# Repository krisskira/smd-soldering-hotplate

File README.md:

# HotPlate

An open SMD reflow station. Instead of heating by eye, it runs a **Soldering Profile**: a precise temperature curve, step by step. It ramps under control, holds each plateau for the right time, signals when it is done and cools down on its own.

[Site](https://krisskira.github.io/smd-soldering-hotplate/) · [HotPanel and Studio](#two-ways-to-run-it) · [Docs](docs/README.md) · [Email](mailto:krisskira@gmail.com) · [Leer en español](README.es.md)

## What it does

- **HEAT** runs the whole profile from one gesture: optional wait, preheat, up to four rising or flat steps, then cooldown.
- **Scheduled start** waits from 00:00 (immediate) up to 12:00 before the cycle begins.
- **Predictive PI** cuts power before the target, so the plate's own inertia does not overshoot.
- **Autotune**, launched from HotPlate Studio, learns how the plate responds and stores the gains.
- **Safety** keeps the heater off at boot. A sensor fault or a reading above `temp_max_c` cuts the output at once.

## Two ways to run it

- **HotPanel**, the onboard interface: a large temperature, two tiles and a knob. Turn to choose, press to confirm. Heat starts or stops the cycle. Settings edits the four steps and the wait clock.
- **HotPlate Studio**, the desktop app over USB: live temperature chart, profile editing, CSV export, autotune and the limits the panel does not expose. When Studio takes control, HotPanel shows **USB** and local input locks. The two modes never run together.

## What's in the repo

- [`firmware/avr/`](firmware/avr/) — ATmega16 firmware at 8 MHz. The map of docs and code starts at [product features](firmware/avr/doc/product_features.md), [program flows](firmware/avr/doc/program_flows.md) and [architecture](firmware/avr/doc/architecture.md).
- [`hotplate-studio/`](hotplate-studio/) — HotPlate Studio (Python). The screens it follows are in [`hotplate-studio/design/`](hotplate-studio/design/).
- [`hardware/`](hardware/) — KiCad board and datasheets.
- [`mechanical/`](mechanical/) — 3D enclosure, covers and knob.
- [`landing-page/`](landing-page/) — the public site, React and TypeScript on Vite.

Flash is 16 KB. Thermal control, safety and the approved UI come first. See the [feature budget](firmware/avr/doc/feature_budget.md).

## Build

```bash
cd firmware/avr && make clean && make && make size && make usb-host-test

cd hotplate-studio && pip install -r requirements.txt && python app.py

cd landing-page && npm install && npm run dev
```

The site publishes to GitHub Pages from `.github/workflows/pages.yml` on every push to `main` that touches `landing-page/`. In the repository: **Settings → Pages → Source: GitHub Actions**.

## License

Open hardware and software. Use, study, modify and share it at your own risk. It works with mains power and high temperatures.

| What | License |
|------|---------|
| Firmware and HotPlate Studio | [MIT](LICENSE) |
| Board and 3D models | [CERN-OHL-P-2.0](LICENSE) |
| Docs and icons | [CC BY 4.0](LICENSE) |

The full text is in [LICENSE](LICENSE).

Author: **Crhistian David Vergara Gómez** · **krisskira@gmail.com**

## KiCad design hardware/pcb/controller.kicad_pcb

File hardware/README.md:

# Hardware

## PCB (`pcb/`)

Proyecto KiCad de **HotPlate**:

- `controller.*` — placa de control (ATmega16, LCD, encoder, MAX31865, …)
- `power-stage.*` — etapa de potencia / SSR
- `smd-soldering-hotplate-pcb.csv` — BOM
- `pcb-cnc/` — exports CNC si aplica

Abrir los `.kicad_pro` con KiCad 8+.

## Datasheets (`datasheets/`)

PDFs de referencia: ATmega16, MAX31865, MOC3021, BT136, ST7920, CH340, HLK-PM01, etc.

Pines de firmware: `firmware/avr/doc/atmega16_pin_definition_hotplate.md` ↔ `firmware/avr/config/board_pins.h`.

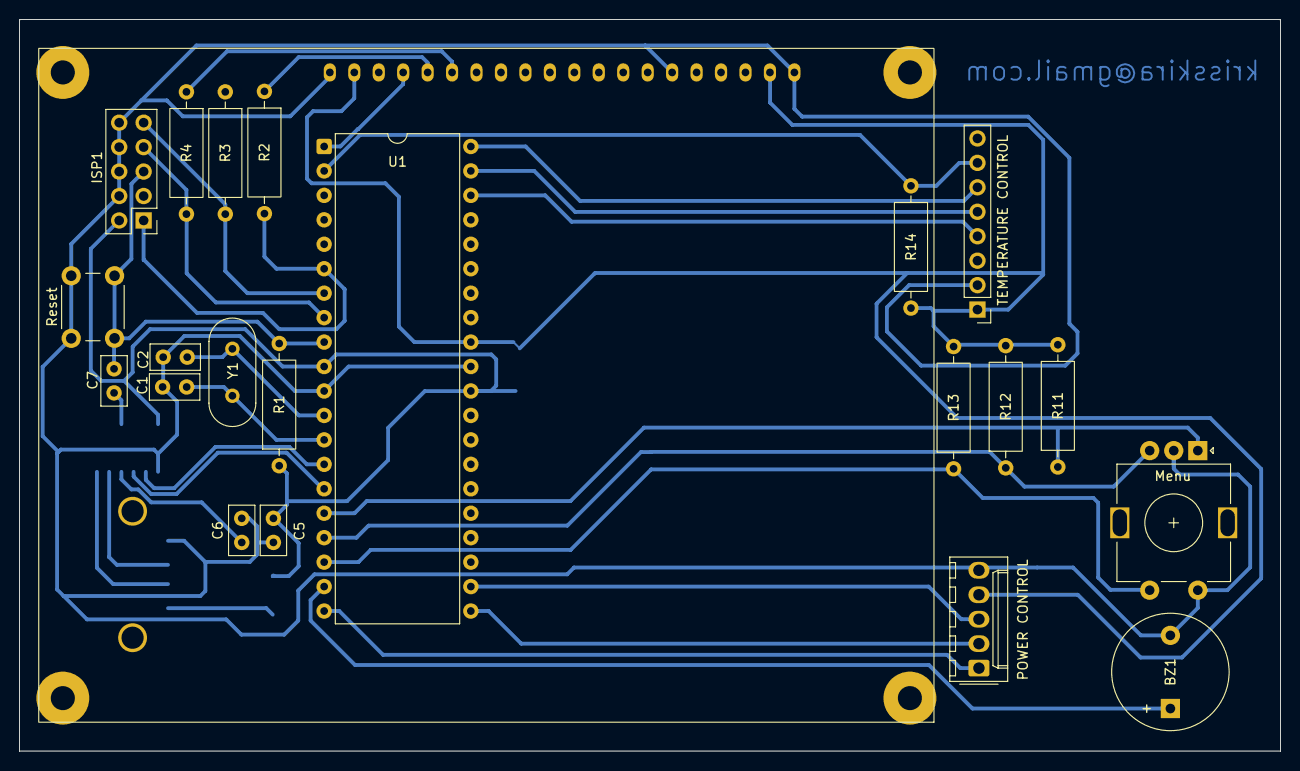
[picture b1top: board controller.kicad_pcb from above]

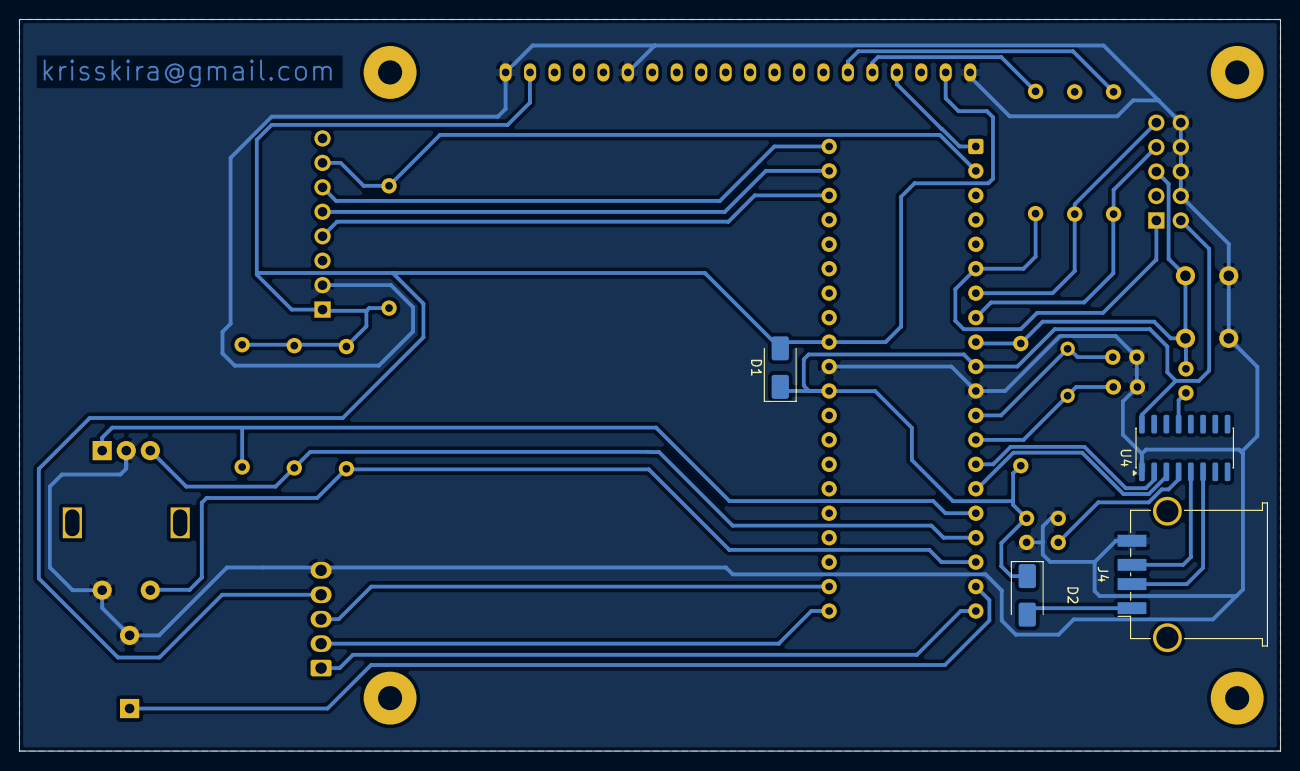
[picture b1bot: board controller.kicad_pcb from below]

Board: 2 copper layers, 131.0 x 76.0 mm, 26 parts (4 on the bottom side), 30 nets.

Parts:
BZ1: Buzzer; Buzzer_12x9.5RM7.6
C1, C2: 27pf; C_Disc_D5.0mm_W2.5mm_P2.50mm
C5, C6: 0.1uF; C_Disc_D5.0mm_W2.5mm_P2.50mm
C7: 100nF; C_Disc_D5.0mm_W2.5mm_P2.50mm
D1, D2: SS14; D_SMA
ISP1: Conn_02x05_Odd_Even; PinHeader_2x05_P2.54mm_Vertical
J4: USB_A; USB_A_TE_292303-7_Horizontal
LCD1: ST7920-12864B; st7920-12864b-v2
Menu: RotaryEncoder_Switch; RotaryEncoder_Alps_EC11E-Switch_Vertical_H20mm
POWER CONTROL: Conn_01x05_Pin; Molex_KK-254_AE-6410-05A_1x05_P2.54mm_Vertical
R1, R3, R4, R11, R12, R13, R14: 10K; R_Axial_DIN0309_L9.0mm_D3.2mm_P12.70mm_Horizontal
R2: 330; R_Axial_DIN0309_L9.0mm_D3.2mm_P12.70mm_Horizontal
Reset: SW_Push_Dual_x2; SW_PUSH_6mm_H5mm
TEMPERATURE CONTROL: Max31865; PinHeader_1x08_P2.54mm_Vertical
U1: ATmega16L-8P; DIP-40_W15.24mm
U4: CH340C; SOIC-16_3.9x9.9mm_P1.27mm
Y1: 16Mhz; Crystal_HC49-4H_Vertical

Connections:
+5V: D1.2 (A), LCD1.2 (VCC), LCD1.19 (BLA), POWER CONTROL.4, R11.2, R12.2, R13.2, R14.2, TEMPERATURE CONTROL.1, U1.32 (AREF)
BUZZER: BZ1.1 (+), U1.19 (PD5)
CS_MAX31865: R14.1, TEMPERATURE CONTROL.7, U1.2 (PB1)
FAN: POWER CONTROL.3, U1.22 (PC0)
GNDREF: BZ1.2 (-), C1.2, C2.2, C5.1, C6.2, ISP1.4, ISP1.6, ISP1.8, ISP1.10, J4.4 (GND), LCD1.1 (GND), LCD1.15 (PSB), LCD1.20 (BLK), Menu.C, Menu.S2, POWER CONTROL.5, Reset.1 (C), TEMPERATURE CONTROL.2, U1.11 (GND), U1.31 (GND), U4.1 (GND)
ICSP_CLK: ISP1.7, R4.2, U1.8 (PB7)
ICSP_MISO: ISP1.9, R3.2, U1.7 (PB6)
ICSP_MOSI: ISP1.1, R2.2, U1.6 (PB5)
ICSP_RST: C7.1, ISP1.5, R1.2, Reset.2 (D), U1.9 (~RESET)
LCD_RS: LCD1.4 (RS(CS*)), U1.1 (PB0)
MENU_CLK: Menu.A, R11.1, U1.16 (PD2)
MENU_DT: Menu.B, R12.1, U1.17 (PD3)
MENU_SW: Menu.S1, R13.1, U1.18 (PD4)
MOSI: LCD1.5 (R/W(SID*)), R2.1
unnamed: D2.2 (A), J4.1 (VBUS)
unnamed: J4.3 (D+), U4.5 (UD+)
unnamed: J4.2 (D-), U4.6 (UD-)
unnamed: C6.1, U4.4 (V3)
unnamed: C7.2, U4.13 (~DTR)
PTC1: POWER CONTROL.2, U1.21 (PD7)
PTC2: POWER CONTROL.1, U1.20 (PD6)
RX: U1.14 (PD0), U4.2 (TXD)
SCK: LCD1.6 (E(SCLK)), R4.1
SOFT_MISO: TEMPERATURE CONTROL.5, U1.39 (PA1)
SOFT_MOSI: TEMPERATURE CONTROL.6, U1.40 (PA0)
SOFT_SCK: TEMPERATURE CONTROL.4, U1.38 (PA2)
TX: U1.15 (PD1), U4.3 (RXD)
V_TARGET: C5.2, D1.1 (K), D2.1 (K), ISP1.2, R1.1, U1.10 (VCC), U1.30 (AVCC), U4.16 (VCC)
xtal1: C1.1, U1.13 (XTAL1), Y1.1
xtal2: C2.1, U1.12 (XTAL2), Y1.2

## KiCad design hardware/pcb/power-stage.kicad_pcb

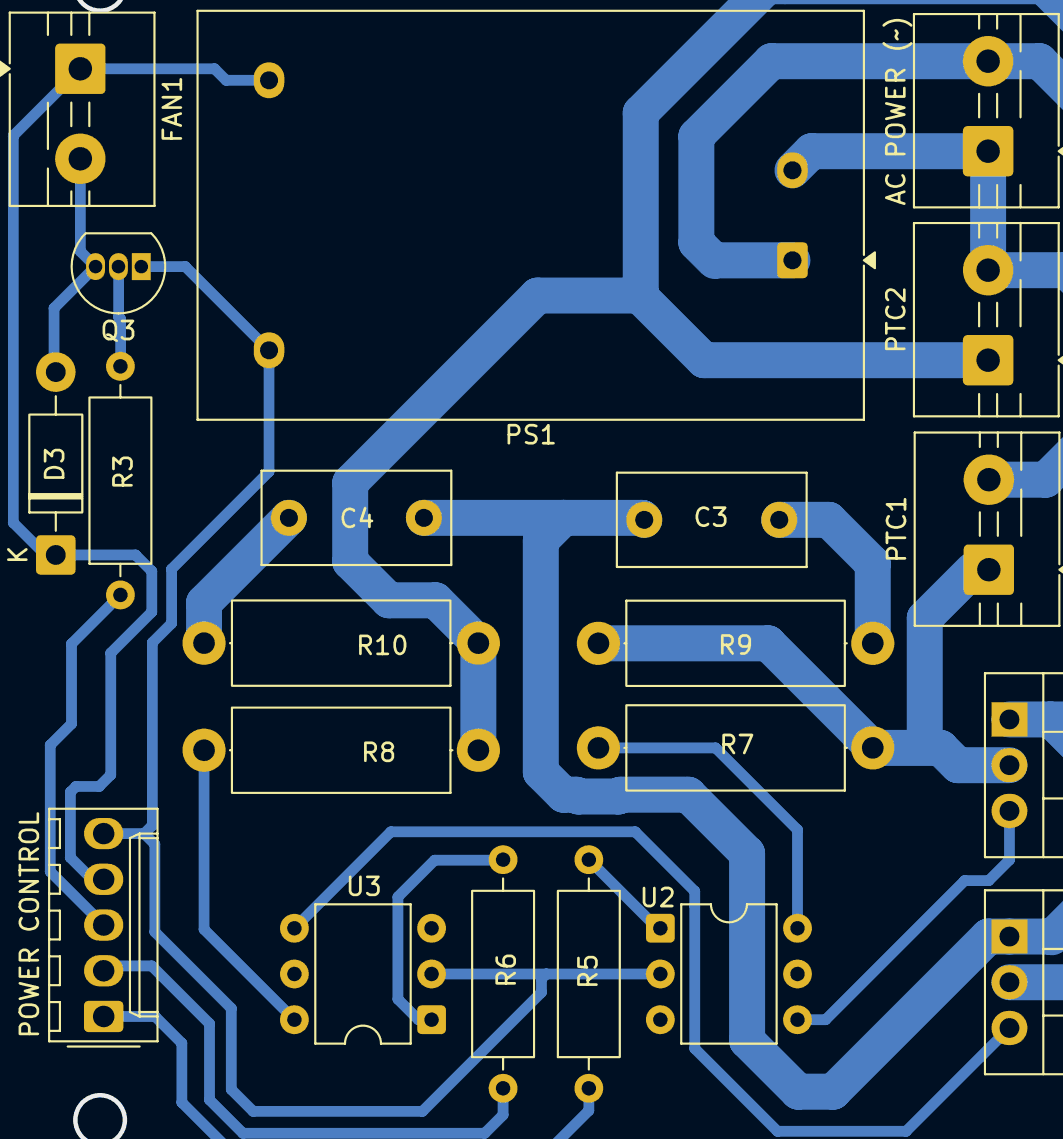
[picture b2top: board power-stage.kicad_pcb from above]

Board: 2 copper layers, 21 parts (0 on the bottom side), 19 nets.

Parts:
AC POWER (~): Screw_Terminal_01x02; TerminalBlock_MaiXu_MX126-5.0-02P_1x02_P5.00mm
C3, C4: 100nf; C_Rect_L10.3mm_W5.0mm_P7.50mm_MKS4
D3: 1N4004; D_DO-41_SOD81_P10.16mm_Horizontal
FAN1: Screw_Terminal_01x02; TerminalBlock_MaiXu_MX126-5.0-02P_1x02_P5.00mm
POWER CONTROL: Conn_01x05_Pin; Molex_KK-254_AE-6410-05A_1x05_P2.54mm_Vertical
PS1: HLK-PM01; Converter_ACDC_Hi-Link_HLK-PMxx
PTC1, PTC2: Screw_Terminal_01x02; TerminalBlock_MaiXu_MX126-5.0-02P_1x02_P5.00mm
Q1, Q2: BT136-600; TO-220-3_Vertical
Q3: 2N2222; TO-92_Inline
R3: 330; R_Axial_DIN0309_L9.0mm_D3.2mm_P12.70mm_Horizontal
R5, R6: 220; R_Axial_DIN0309_L9.0mm_D3.2mm_P12.70mm_Horizontal
R7, R8, R9, R10: 100; R_Axial_DIN0414_L11.9mm_D4.5mm_P15.24mm_Horizontal
U2, U3: MOC3021M; DIP-6_W7.62mm

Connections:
LINE: AC POWER (~).1, PS1.2 (AC/N), PTC1.2, PTC2.2
NEUTRO: AC POWER (~).2, C3.2, C4.2, PS1.1 (AC/L), Q1.1 (A1), Q2.1 (A1)
unnamed: C3.1, R9.2
unnamed: C4.1, R10.2
unnamed: D3.2 (A), FAN1.2, Q3.3 (C)
unnamed: PTC1.1, Q1.2 (A2), R7.1, R9.1
unnamed: PTC2.1, Q2.2 (A2), R8.1, R10.1
unnamed: Q1.3 (G), U2.4
unnamed: Q2.3 (G), U3.4
unnamed: Q3.2 (B), R3.2
unnamed: R5.2, U2.1
unnamed: R6.2, U3.1
unnamed: R7.2, U2.6
unnamed: R8.2, U3.6
P_FAN: POWER CONTROL.3, R3.1
P_GND: POWER CONTROL.5, PS1.3 (-Vout), Q3.1 (E), U2.2, U3.2
P_PTC1: POWER CONTROL.1, R5.1
P_PTC2: POWER CONTROL.2, R6.1
P_VCC: D3.1 (K), FAN1.1, POWER CONTROL.4, PS1.4 (+Vout)

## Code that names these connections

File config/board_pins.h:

#ifndef BOARD_PINS_H
#define BOARD_PINS_H

#include <avr/io.h>

/*
 * Mapa de pines del ATmega16 — SMI Soldering Hot Plate.
 * Fuente de verdad para SPI, CS y actuadores. F_CPU oficial: 8 MHz
 * (lo define el Makefile; cristal de la placa según BOM puede diferir,
 * pero el firmware se compila y temporiza a 8 MHz).
 */

/* ---------- SPI hardware (LCD ST7920) — PORTB ------------------------ */

#define SPI_PORT PORTB
#define SPI_DDR  DDRB

#define SPI_MOSI PB5
#define SPI_MISO PB6
#define SPI_SCK  PB7

/* ---------- SPI software (MAX31865) — PORTA -------------------------- */

#define SOFT_SPI_MOSI  PA0
#define SOFT_SPI_MISO  PA1
#define SOFT_SPI_SCK   PA2
#define SOFT_SPI_DDR   DDRA
#define SOFT_SPI_PORT  PORTA
#define SOFT_SPI_PIN   PINA

/* ---------- Chip Selects --------------------------------------------- */

#define LCD_CS_PORT PORTB
#define LCD_CS_DDR  DDRB
#define LCD_CS_PIN  PB0

#define MAX31865_CS_PORT PORTB
#define MAX31865_CS_DDR  DDRB
#define MAX31865_CS_PIN  PB1

/* ---------- Encoder (PORTD) ------------------------------------------ */

#define ENC_PORT  PORTD
#define ENC_DDR   DDRD
#define ENC_PINR  PIND
#define ENC_A     PD2       /* CLK */
#define ENC_B     PD3       /* DT  */
#define ENC_SW    PD4       /* pulsador, activo bajo */

/*
 * Semántica de encoder_poll():
 *   +1 = un click en sentido HORARIO  → cursor baja en el menú
 *   -1 = un click en sentido ANTIHORARIO → cursor sube
 *
 * Si el cableado A/B está invertido respecto a la mecánica, pon 0.
 */
#define ENC_CW_IS_POSITIVE  1

/* ---------- Actuadores ----------------------------------------------- */

/* Calefactores (esquemático: PTC1=PD7 pin21, PTC2=PD6 pin20) */
#define PTC1_PORT PORTD
#define PTC1_DDR  DDRD
#define PTC1_PIN  PD7

#define PTC2_PORT PORTD
#define PTC2_DDR  DDRD
#define PTC2_PIN  PD6

/* Bomba de aire / ventilador (esquemático: FAN=PC0 pin22) */
#define FAN_PORT  PORTC
#define FAN_DDR   DDRC
#define FAN_PIN   PC0

/* Buzzer */
#define BUZZER_PORT PORTD
#define BUZZER_DDR  DDRD
#define BUZZER_PIN  PD5

#endif

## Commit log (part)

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2026-03-06 chore(lcd): build basic driver
2026-03-07 feat: enhance README and add non-blocking animation strategy
    - Updated README.md to include details on non-blocking animations for the ST7920 LCD, including new API functions and documentation links.
    - Added new documentation file for non-blocking animation strategies.
    - Introduced .vscode/tasks.json for build and clean tasks.
    - Added multiple animated icons (automation, copy, normal distribution histogram, notes, plot, temperature) with optimized frame data.
2026-03-08 feat: implement non-blocking animation management and GDRAM region handling
    - Added `st7920_animation_run` and `st7920_animation_run_all` for managing multiple animations without blocking the main loop.
    - Introduced `st7920_clear_region` and `st7920_draw_region_pgm` to handle clearing and replacing regions in GDRAM, enhancing UI flexibility.
    - Updated documentation to reflect new features and usage patterns for non-blocking animations and GDRAM management.
    - Modified main loop to utilize new animation management functions and direct text drawing in GDRAM.
2026-03-08 feat: add MAX31865 sensor support and improve Makefile for debug builds
    - Introduced MAX31865 library for PT100/P1000 RTD sensor, including initialization, reading, and temperature conversion functions.
    - Updated Makefile to support both normal and debug builds, allowing for separate compilation of main and debug source files.
    - Modified board_pins.h to reflect changes in chip select pins for LCD and MAX31865.
    - Enhanced main.c to integrate MAX31865 readings and display temperature on ST7920 LCD.
    - Added new functions for buzzer and PTC control in ports library.
2026-03-08 refactor: update README and documentation for SPI and non-blocking timing
    - Enhanced README.md with detailed descriptions of SPI hardware and software configurations for the ST7920 and MAX31865.
    - Added a new documentation file for non-blocking timing strategies, providing examples and usage patterns.
    - Updated board_pins.h to clarify pin assignments for SPI hardware and software.
    - Improved documentation links across various files for better navigation and understanding of the system architecture.
